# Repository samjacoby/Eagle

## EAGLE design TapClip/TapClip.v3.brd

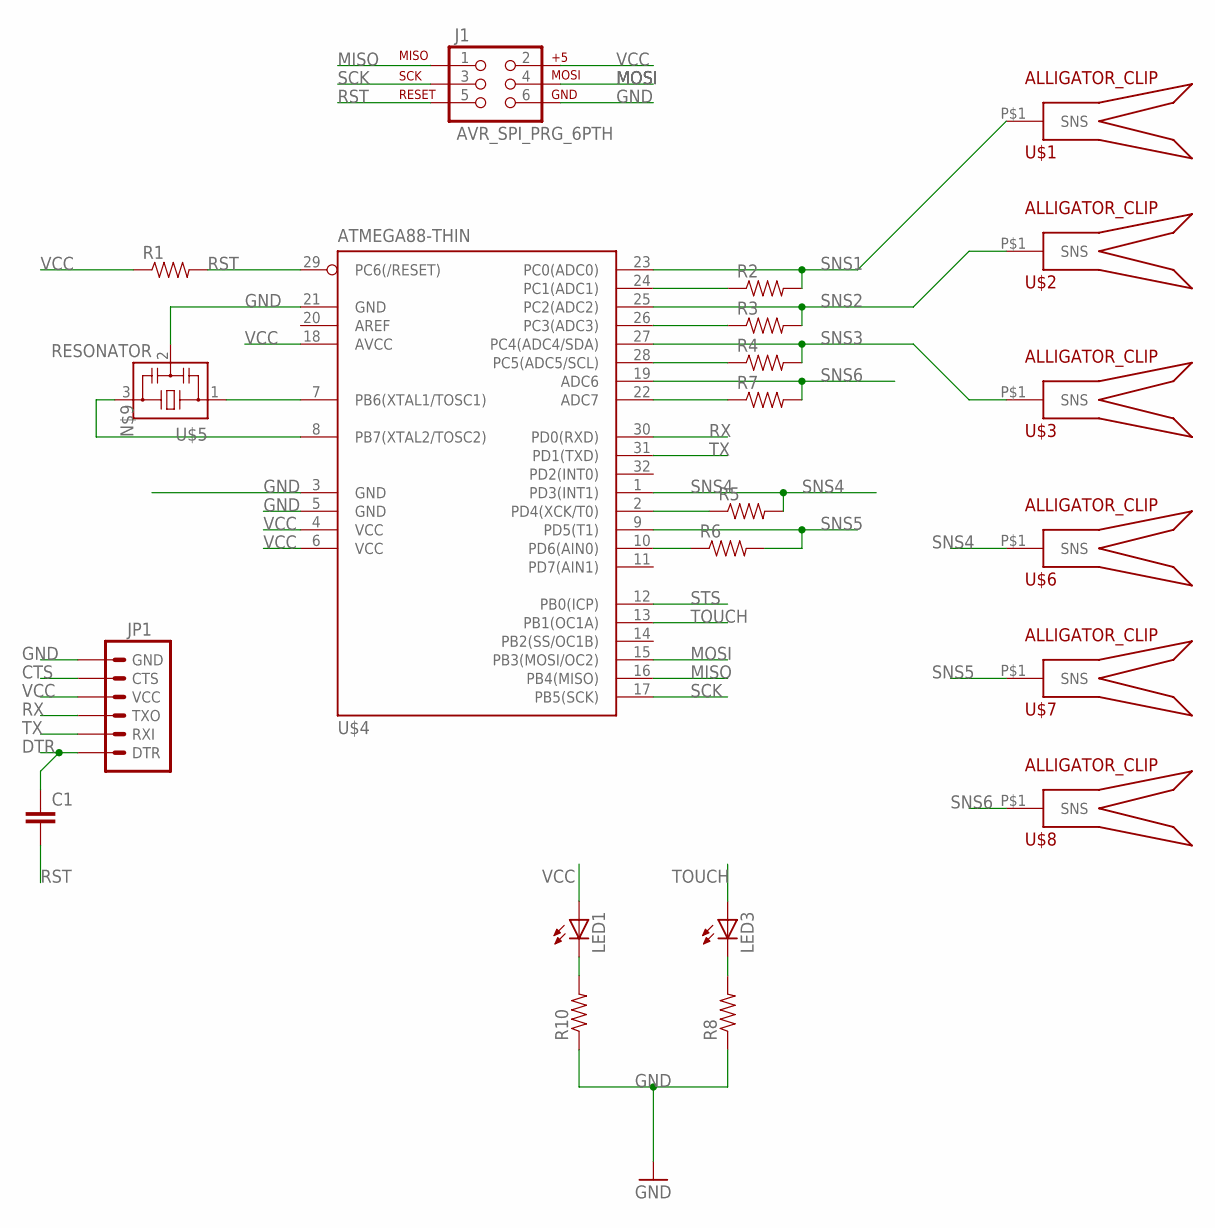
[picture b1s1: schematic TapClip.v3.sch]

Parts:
C1: CAP0603-CAP; 0603-CAP
J1: AVR_SPI_PRG_6PTH; 2X3
JP1: ARDUINO_SERIAL_PROGRAMSMD; 1X06-SMD
LED1, LED3: LED1206; LED-1206
R1, R2, R3, R4, R5, R6, R7: RESISTOR0603-RES; 0603-RES
R8, R10: RESISTOR1206; 1206
U$1, U$2, U$3, U$6, U$7, U$8: ALLIGATOR_CLIP
U$4: ATMEGA88-THIN; TQFP32-08THIN
U$5: RESONATOR; EFOBM

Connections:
CTS: JP1.5 (CTS)
DTR: C1.1, JP1.1 (DTR)
GND: J1.6, JP1.6 (GND), R8.1, R10.1, U$4.3 (GND), U$4.5 (GND), U$4.21 (GND), U$5.2
MISO: J1.1, U$4.16 (PB4(MISO))
MOSI: J1.4, U$4.15 (PB3(MOSI/OC2))
unnamed: R2.1, U$4.24 (PC1(ADC1))
unnamed: LED1.C, R10.2
unnamed: R3.1, U$4.26 (PC3(ADC3))
unnamed: R4.1, U$4.28 (PC5(ADC5/SCL))
unnamed: LED3.C, R8.2
unnamed: U$4.8 (PB7(XTAL2/TOSC2)), U$5.3
unnamed: U$4.7 (PB6(XTAL1/TOSC1)), U$5.1
unnamed: R5.1, U$4.2 (PD4(XCK/T0))
unnamed: R6.1, U$4.10 (PD6(AIN0))
unnamed: R7.1, U$4.22 (ADC7)
RST: C1.2, J1.5, R1.2, U$4.29 (PC6(/RESET))
RX: JP1.3 (TXO), U$4.30 (PD0(RXD))
SCK: J1.3, U$4.17 (PB5(SCK))
SNS1: R2.2, U$1.P$1, U$4.23 (PC0(ADC0))
SNS2: R3.2, U$2.P$1, U$4.25 (PC2(ADC2))
SNS3: R4.2, U$3.P$1, U$4.27 (PC4(ADC4/SDA))
SNS4: R5.2, U$4.1 (PD3(INT1)), U$6.P$1
SNS5: R6.2, U$4.9 (PD5(T1)), U$7.P$1
SNS6: R7.2, U$4.19 (ADC6), U$8.P$1
STS: U$4.12 (PB0(ICP))
TOUCH: LED3.A, U$4.13 (PB1(OC1A))
TX: JP1.2 (RXI), U$4.31 (PD1(TXD))
VCC: J1.2, JP1.4 (VCC), LED1.A, R1.1, U$4.4 (VCC), U$4.6 (VCC), U$4.18 (AVCC)

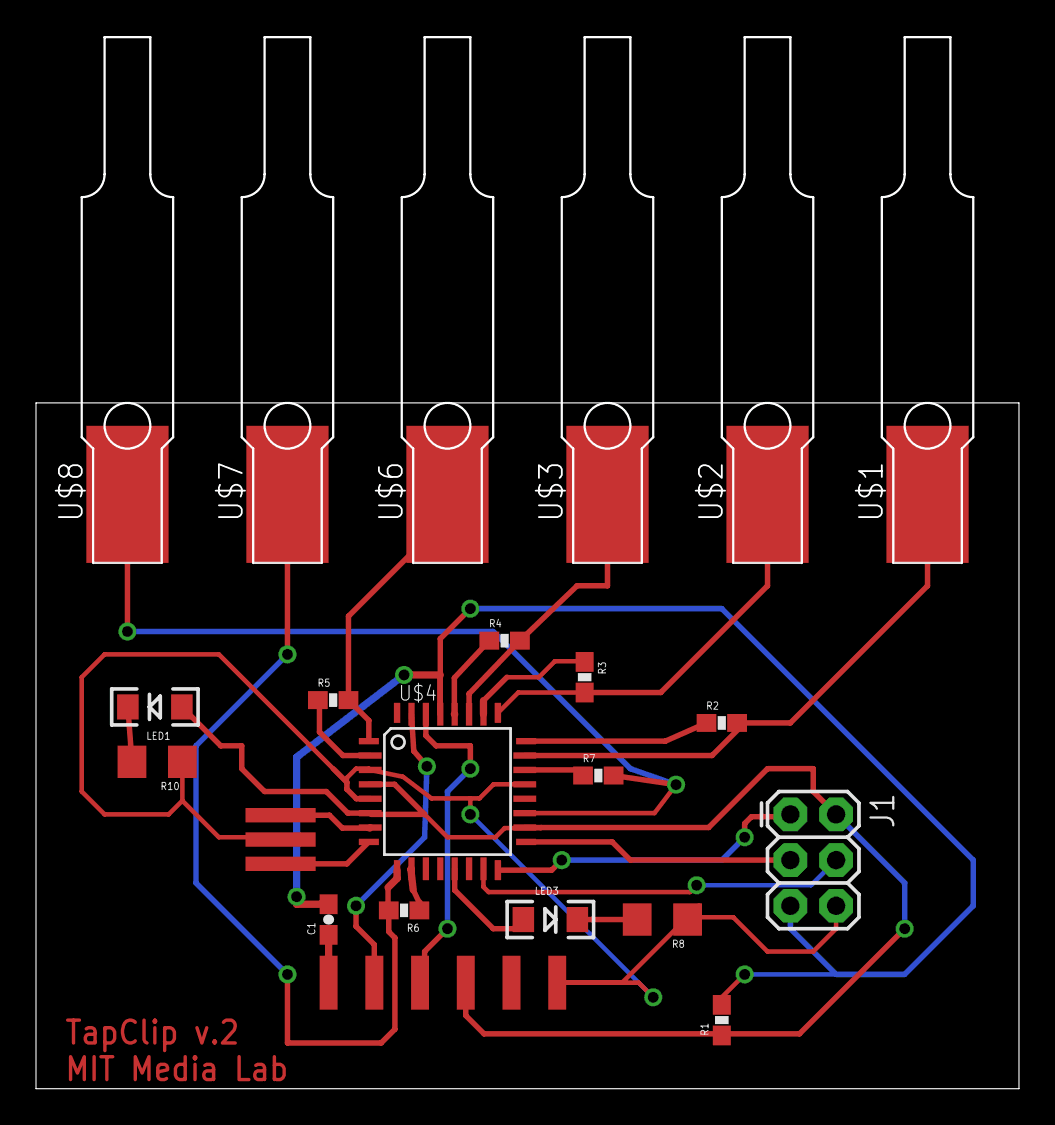
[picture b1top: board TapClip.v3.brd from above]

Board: 2 copper layers, 54.6 x 38.1 mm, 22 parts (0 on the bottom side), 26 nets.

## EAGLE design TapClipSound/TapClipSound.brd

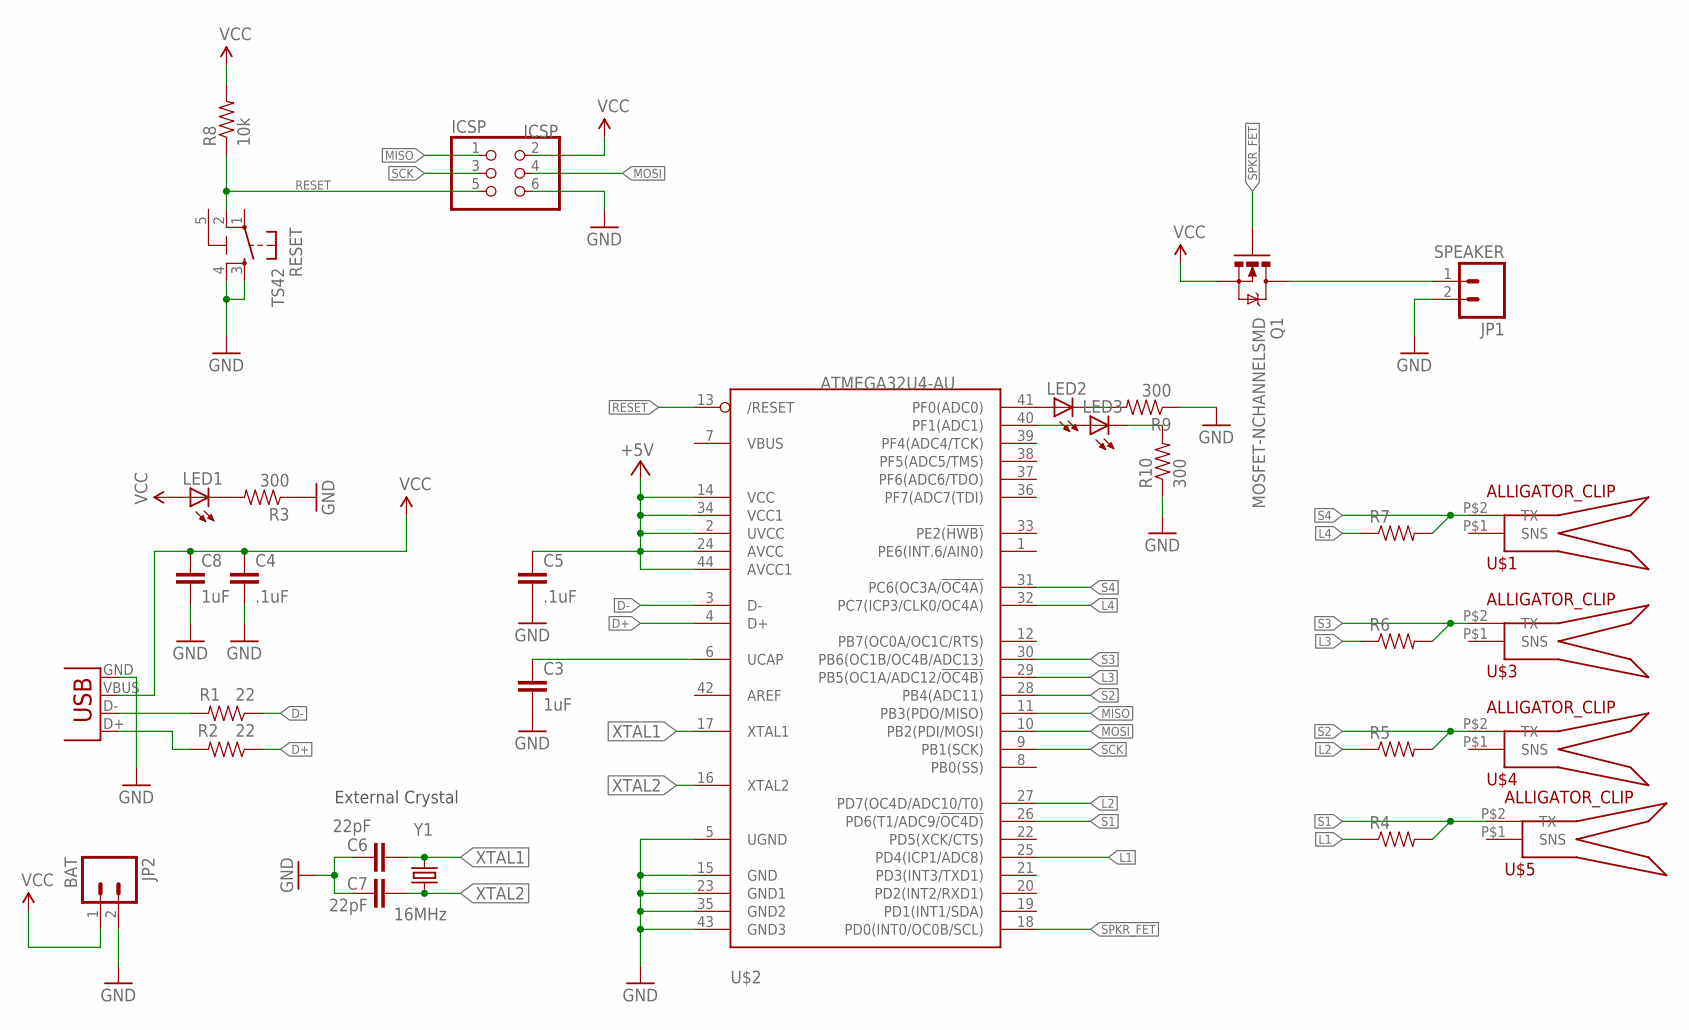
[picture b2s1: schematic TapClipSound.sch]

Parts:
C3, C8: 1uF; 0603-CAP
C4, C5: .1uF; 0603-CAP
C6, C7: 22pF; 0402-CAP
ICSP: ICSP; 2X03
JP1: SPEAKER; 1X02_LOCK_LONGPADS
JP2: BAT; 1X02_LOCK_LONGPADS
LED1, LED2, LED3: LED0603; LED-0603
Q1: MOSFET-NCHANNELSMD; SOT23-3
R1, R2: 22; 0402-RES
R3, R9, R10: 300; 0603-RES
R4, R5, R6, R7: RESISTOR0603-RES; 0603-RES
R8: 10k; 0603-RES
RESET: TS42
U$1, U$3, U$4, U$5: ALLIGATOR_CLIP
U$2: ATMEGA32U4-AU; TQFP44
X1: USBSMD; USB-MINIB
Y1: 16MHz; CRYSTAL-SMD-5X3

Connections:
5-GND: RESET.5 (5-GND)
D+: R2.1, U$2.4 (D+)
D-: R1.1, U$2.3 (D-)
GND: C3.2, C4.2, C5.2, C6.2, C7.2, C8.2, ICSP.6, JP1.2, JP2.2, R3.1, R9.1, R10.1, RESET.3, RESET.4, U$2.5 (UGND), U$2.15 (GND), U$2.23 (GND1), U$2.35 (GND2), U$2.43 (GND3), X1.GND
L1: R4.1, U$2.25 (PD4(ICP1/ADC8))
L2: R5.1, U$2.27 (PD7(OC4D/ADC10/T0))
L3: R6.1, U$2.29 (PB5(OC1A/ADC12/!OC4B))
L4: R7.1, U$2.32 (PC7(ICP3/CLK0/OC4A))
MISO: ICSP.1, U$2.11 (PB3(PDO/MISO))
MOSI: ICSP.4, U$2.10 (PB2(PDI/MOSI))
unnamed: C3.1, U$2.6 (UCAP)
unnamed: LED1.C, R3.2
unnamed: JP1.1, Q1.3 (D)
unnamed: LED2.C, R9.2
unnamed: LED2.A, U$2.41 (PF0(ADC0))
unnamed: R1.2, X1.D-
unnamed: LED3.C, R10.2
unnamed: R2.2, X1.D+
unnamed: LED3.A, U$2.40 (PF1(ADC1))
RESET: ICSP.5, R8.1, RESET.2, U$2.13 (/RESET)
S1: R4.2, U$2.26 (PD6(T1/ADC9/!OC4D)), U$5.P$2 (TX)
S2: R5.2, U$2.28 (PB4(ADC11)), U$4.P$2 (TX)
S3: R6.2, U$2.30 (PB6(OC1B/OC4B/ADC13)), U$3.P$2 (TX)
S4: R7.2, U$1.P$2 (TX), U$2.31 (PC6(OC3A/!OC4A))
SCK: ICSP.3, U$2.9 (PB1(SCK))
SPKR_FET: Q1.1 (G), U$2.18 (PD0(INT0/OC0B/SCL))
VCC: C4.1, C5.1, C8.1, ICSP.2, JP2.1, LED1.A, Q1.2 (S), R8.2, U$2.2 (UVCC), U$2.14 (VCC), U$2.24 (AVCC), U$2.34 (VCC1), U$2.44 (AVCC1), X1.VBUS
XTAL1: C6.1, U$2.17 (XTAL1), Y1.3 (2)
XTAL2: C7.1, U$2.16 (XTAL2), Y1.1

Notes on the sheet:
External Crystal

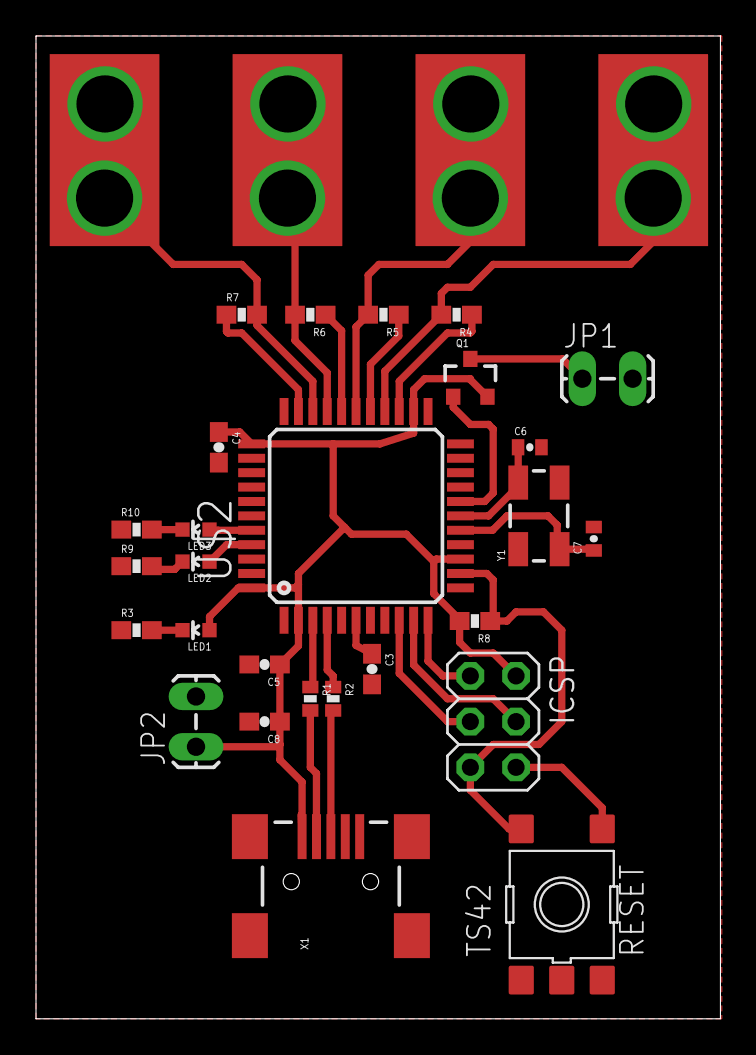
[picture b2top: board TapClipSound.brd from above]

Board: 2 copper layers, 38.0 x 54.6 mm, 31 parts (0 on the bottom side), 28 nets.

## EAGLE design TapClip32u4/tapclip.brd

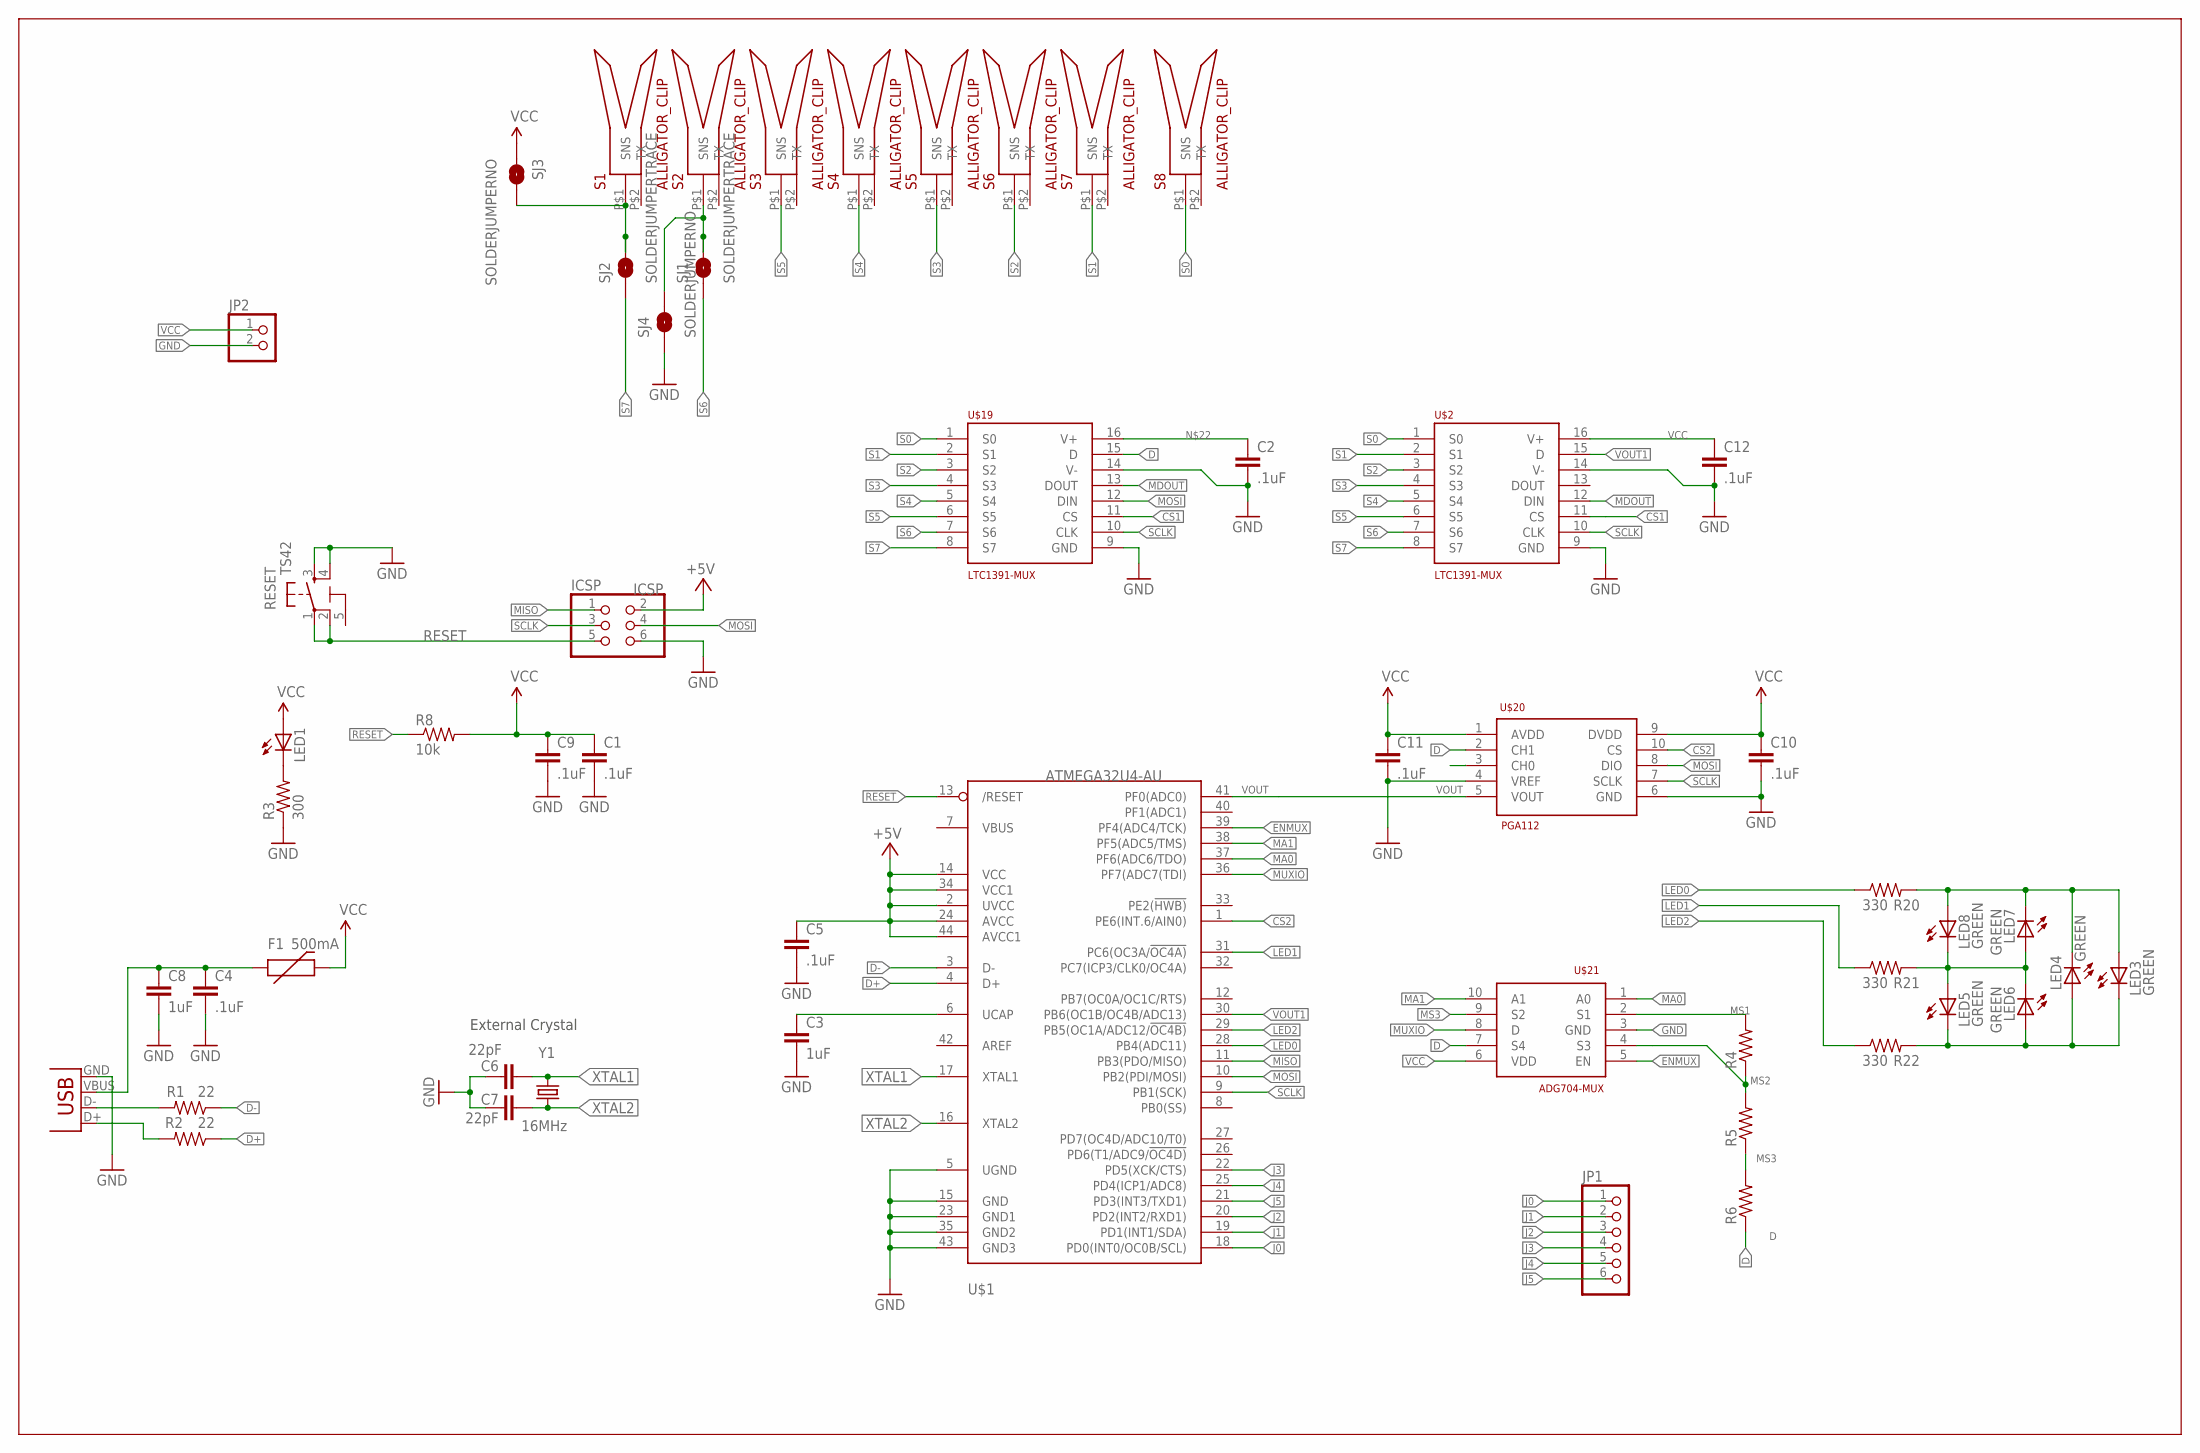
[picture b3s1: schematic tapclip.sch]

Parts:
C1, C2, C4, C5, C9, C10, C11, C12: .1uF; 0603-CAP
C3, C8: 1uF; 0603-CAP
C6, C7: 22pF; 0402-CAP
F1: 500mA; PTC-1206
ICSP: ICSP; 2X03
JP1: PINHD-1X6CB; 1X06-CLEANBIG
JP2: PINHD-1X2; 1X02
LED1: LED0603; LED-0603
LED3, LED4, LED5, LED6, LED7, LED8: GREEN; LED-0603
R1, R2: 22; 0402-RES
R3: 300; 0603-RES
R4, R5, R6: RESISTOR0603-RES; 0603-RES
R8: 10k; 0603-RES
R20, R21, R22: 330; 0402-RES
RESET: TS42
S1, S2, S3, S4, S5, S6, S7, S8: ALLIGATOR_CLIP
SJ1, SJ2: SOLDERJUMPERTRACE; SJ_2S-TRACE
SJ3, SJ4: SOLDERJUMPERNO; SJ_2S-NO
U$1: ATMEGA32U4-AU; TQFP44
U$2, U$19: LTC1391-MUX; SOIC16N
U$20: PGA112; MICROSOIC10
U$21: ADG704-MUX; MICROSOIC10
X1: USBSMD; USB-MINIB
Y1: 16MHz; CRYSTAL-SMD-5X3

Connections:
5-GND: RESET.5 (5-GND)
CS1: U$2.11 (CS), U$19.11 (CS)
CS2: U$1.1 (PE6(INT.6/AIN0)), U$20.10 (CS)
D: R6.1, U$19.15 (D), U$20.2 (CH1), U$21.7 (S4)
D+: R2.1, U$1.4 (D+)
D-: R1.1, U$1.3 (D-)
ENMUX: U$1.39 (PF4(ADC4/TCK)), U$21.5 (EN)
GND: C1.2, C2.2, C3.2, C4.2, C5.2, C6.2, C7.2, C8.2, C9.2, C10.2, C11.2, C12.2, ICSP.6, JP2.2, R3.1, RESET.3, RESET.4, SJ4.1, U$1.5 (UGND), U$1.15 (GND), U$1.23 (GND1), U$1.35 (GND2), U$1.43 (GND3), U$2.9 (GND), U$2.14 (V-), U$19.9 (GND), U$19.14 (V-), U$20.4 (VREF), U$20.6 (GND), U$21.3 (GND), X1.GND
J0: JP1.1, U$1.18 (PD0(INT0/OC0B/SCL))
J1: JP1.2, U$1.19 (PD1(INT1/SDA))
J2: JP1.3, U$1.20 (PD2(INT2/RXD1))
J3: JP1.4, U$1.22 (PD5(XCK/CTS))
J4: JP1.5, U$1.25 (PD4(ICP1/ADC8))
J5: JP1.6, U$1.21 (PD3(INT3/TXD1))
LED0: R20.1, U$1.28 (PB4(ADC11))
LED1: R21.1, U$1.31 (PC6(OC3A/!OC4A))
LED2: R22.1, U$1.29 (PB5(OC1A/ADC12/!OC4B))
MA0: U$1.37 (PF6(ADC6/TDO)), U$21.1 (A0)
MA1: U$1.38 (PF5(ADC5/TMS)), U$21.10 (A1)
MDOUT: U$2.12 (DIN), U$19.13 (DOUT)
MISO: ICSP.1, U$1.11 (PB3(PDO/MISO))
MOSI: ICSP.4, U$1.10 (PB2(PDI/MOSI)), U$19.12 (DIN), U$20.8 (DIO)
MS1: R4.2, U$21.2 (S1)
MS2: R4.1, R5.2, U$21.4 (S3)
MS3: R5.1, R6.2, U$21.9 (S2)
MUXIO: U$1.36 (PF7(ADC7(TDI)), U$21.8 (D)
unnamed: C3.1, U$1.6 (UCAP)
unnamed: LED1.C, R3.2
unnamed: C4.1, C8.1, F1.1, X1.VBUS
unnamed: R1.2, X1.D-
unnamed: R2.2, X1.D+
unnamed: S1.P$1 (SNS), SJ2.2, SJ3.2
unnamed: S2.P$1 (SNS), SJ1.2, SJ4.2
unnamed: C2.1, U$19.16 (V+)
unnamed: LED5.A, LED6.C, LED7.A, LED8.C, R21.2
unnamed: LED3.A, LED4.C, LED7.C, LED8.A, R20.2
unnamed: LED3.C, LED4.A, LED5.C, LED6.A, R22.2
RESET: ICSP.5, R8.1, RESET.1, RESET.2, U$1.13 (/RESET)
S0: S8.P$1 (SNS), U$2.1 (S0), U$19.1 (S0)
S1: S7.P$1 (SNS), U$2.2 (S1), U$19.2 (S1)
S2: S6.P$1 (SNS), U$2.3 (S2), U$19.3 (S2)
S3: S5.P$1 (SNS), U$2.4 (S3), U$19.4 (S3)
S4: S4.P$1 (SNS), U$2.5 (S4), U$19.5 (S4)
S5: S3.P$1 (SNS), U$2.6 (S5), U$19.6 (S5)
S6: SJ1.1, U$2.7 (S6), U$19.7 (S6)
S7: SJ2.1, U$2.8 (S7), U$19.8 (S7)
SCLK: ICSP.3, U$1.9 (PB1(SCK)), U$2.10 (CLK), U$19.10 (CLK), U$20.7 (SCLK)
VCC: C1.1, C5.1, C9.1, C10.1, C11.1, C12.1, F1.2, ICSP.2, JP2.1, LED1.A, R8.2, SJ3.1, U$1.2 (UVCC), U$1.14 (VCC), U$1.24 (AVCC), U$1.34 (VCC1), U$1.44 (AVCC1), U$2.16 (V+), U$20.1 (AVDD), U$20.9 (DVDD), U$21.6 (VDD)
VOUT: U$1.41 (PF0(ADC0)), U$20.5 (VOUT)
VOUT1: U$1.30 (PB6(OC1B/OC4B/ADC13)), U$2.15 (D)
XTAL1: C6.1, U$1.17 (XTAL1), Y1.3 (2)
XTAL2: C7.1, U$1.16 (XTAL2), Y1.1

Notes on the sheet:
External Crystal

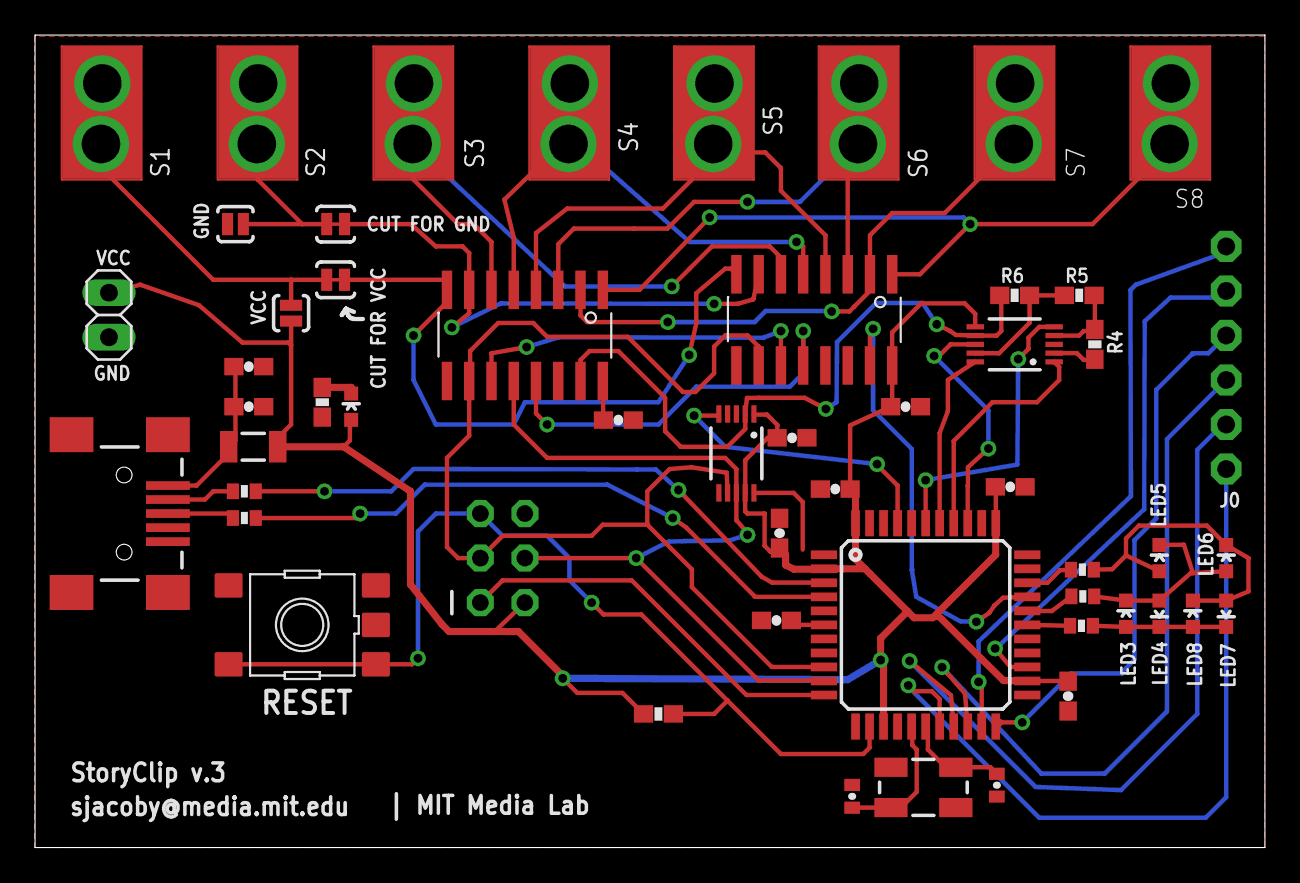
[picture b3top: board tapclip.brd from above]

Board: 2 copper layers, 70.2 x 46.3 mm, 53 parts (1 on the bottom side), 51 nets.

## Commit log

2012-10-30 It's time to start doing this.
2012-10-30 For historic synchronicity.
2012-10-30 Onward, ye sons of man.
2012-10-30 Libraries, in from the cold.
2012-10-30 Keeping up with the Jones's
2012-11-01 Much has taken place here. Be still. Breath. Prepare yonder Gerbers.
2012-11-01 Gerbers, for whatever reason, are sacred.
2012-11-01 And we've entered the rodeo.
2012-11-01 Here we list the moments of our passage. Spirit, breathe, motion.
2012-12-01 This is the place where we are.
2012-12-01 These are the things that should be done for this.
2013-01-13 Adding board w/ sound.

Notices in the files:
parts and their libraries:
SparkFun: Licensing: CC v3.0 Share-Alike You are welcome to use this library for commercial purposes.
